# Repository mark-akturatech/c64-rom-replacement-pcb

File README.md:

# Commodore 64 Kernal Replacement Project

## Description

Simple and compact PCB to replace the C64 Kernal (this is how Commodore spell Kernel) ROM with a 27C256 with the original ROM dump and 3 additional alternative ROMs.

## Development

The project is constructed in Kicad. The output files are generated in Gerber format.

## Design

The PCB replaces the Kernal ROM. The PCB plugs in to the Kernal ROM socket. Two switches or a rotary switch may be used to switch between the alternative ROMs.

## EPROM Configuration

The EPROM is segmented as follows:

- 0k-8k Original Kernal ROM (bank 1) Address line 13 LOW; Address line 14 LOW
- 8k-16k Jiffy DOS (bank 2) Address line 13 HIGH; Address line 14 LOW
- 16k-24k Cockroach Turbo ROM [nostalgia reasons] (bank 3) Address line 13 LOW; Address line 14 HIGH
- 24k-32k Dolphin DOS (bank 4) Address line 13 HIGH; Address line 14 HIGH

The ROM configuration I have used is as follows:

- 0k-8k kernal.901227-03
- 8k-16k JiffyDOS_C64
- 16k-24k cockroach_turbo_rom
- 24k-32k dolphin_dos-30

A switch is connected between +5v and address lines 13 adn 14.

## Part List & Build Instructions

2 x 20 contact (only need 12 contact by 20 is more common) Board-to-Board through hole straight pin headers.
For example <https://au.element14.com/amp-te-connectivity/2-826629-0/btb-conn-header-20pos-1row-2-54mm/dp/1580047>
These are soldered to the 2 rows of 12 through-holes on the underside of the board and are used to plug in to the Kernal ROM socket.
Solder these first.

1 x 28 contact DIP 2.5mm x 15.24mm socket. The socket should slightly stand off the board to not interfere with the pin headers.
For example <https://au.element14.com/multicomp/2227mc-28-06-07-f1/socket-ic-dil-0-6-28way/dp/1103852>
This soldered to the topside of the PCB for mounting the 27C256.

1 x 4 position, minimum 2 pole rotary switch or 2 x single throw double miniature toggle switches
For example <https://au.mouser.com/ProductDetail/Alpha-Taiwan/SR2511F-0304-19R0B-E9-N-W-159> OR
<https://au.element14.com/e-switch/100sp1t1b1m1qeh/toggle-switch-spdt-5a-120vac-28vdc/dp/2522278>

1 x 27C256 EPROM (or compatible - eg AT28C256 will also work)
I've used a write once compatible EPROM here.

## Rotary Switch Wiring

If a 4 position rotary switch is used, it is wired as follows:
- Pole A: connected to address line 13
- Pole B: connected to address line 14
- Pins 1, 3, 5 and 6 connected to GND
- Pins 2, 4, 7 and 8 connected to +5V

This should result in the following truth table:
Pos | A13 | A14 | Why
--- | --- | --- | ---
1 | L | L | Pin 1 (Pole A Way 1) Low, Pin 5 (Pole B Way 1) Low
2 | H | L | Pin 2 (Pole A Way 2) High, Pin 6 (Pole B Way 2) Low
3 | L | H | Pin 3 (Pole A Way 3) Low, Pin 7 (Pole B Way 3) High
4 | H | H | Pin 4 (Pole A Way 4) High, Pin 8 (Pole B Way 4) High

## Double Pole Switch Wiring

If using two single throw double pole switches, wire as follows:
- Switch 1: Center pin to address line 13, top pin to GND, bottom pin to +5V.
- Switch 2: Center pin to address line 14, top pin to GND, bottom pin to +5V.

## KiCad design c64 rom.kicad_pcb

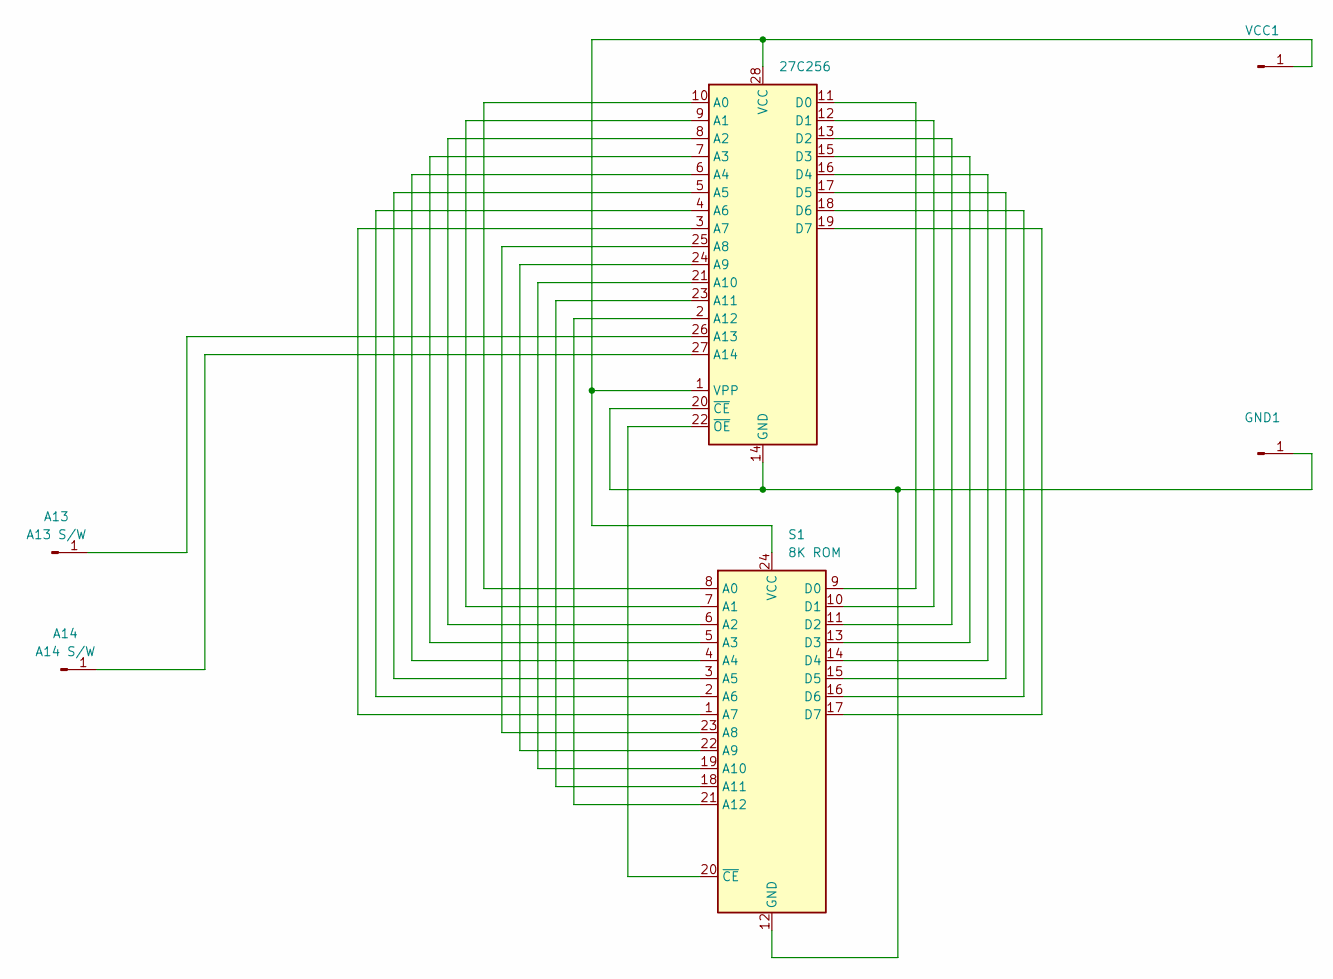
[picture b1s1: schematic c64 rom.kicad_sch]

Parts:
A13: A13 S/W; Pin_D0.7mm_L6.5mm_W1.8mm_FlatFork
A14: A14 S/W; Pin_D0.7mm_L6.5mm_W1.8mm_FlatFork
GND1: GND; Pin_D0.7mm_L6.5mm_W1.8mm_FlatFork
S1: 8K ROM; DIP-24_W15.24mm
U1: 27C256; DIP-28_W15.24mm
VCC1: +5V; Pin_D0.7mm_L6.5mm_W1.8mm_FlatFork

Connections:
unnamed: A13.1, U1.26 (A13)
unnamed: A14.1, U1.27 (A14)
unnamed: GND1.1, S1.12 (GND), U1.14 (GND), U1.20 (~CE)
unnamed: S1.8 (A0), U1.10 (A0)
unnamed: S1.7 (A1), U1.9 (A1)
unnamed: S1.6 (A2), U1.8 (A2)
unnamed: S1.5 (A3), U1.7 (A3)
unnamed: S1.4 (A4), U1.6 (A4)
unnamed: S1.3 (A5), U1.5 (A5)
unnamed: S1.2 (A6), U1.4 (A6)
unnamed: S1.1 (A7), U1.3 (A7)
unnamed: S1.23 (A8), U1.25 (A8)
unnamed: S1.22 (A9), U1.24 (A9)
unnamed: S1.19 (A10), U1.21 (A10)
unnamed: S1.18 (A11), U1.23 (A11)
unnamed: S1.21 (A12), U1.2 (A12)
unnamed: S1.9 (D0), U1.11 (D0)
unnamed: S1.10 (D1), U1.12 (D1)
unnamed: S1.11 (D2), U1.13 (D2)
unnamed: S1.13 (D3), U1.15 (D3)
unnamed: S1.14 (D4), U1.16 (D4)
unnamed: S1.15 (D5), U1.17 (D5)
unnamed: S1.16 (D6), U1.18 (D6)
unnamed: S1.17 (D7), U1.19 (D7)
unnamed: S1.24 (VCC), U1.1 (VPP), U1.28 (VCC), VCC1.1
unnamed: S1.20 (~CE), U1.22 (~OE)

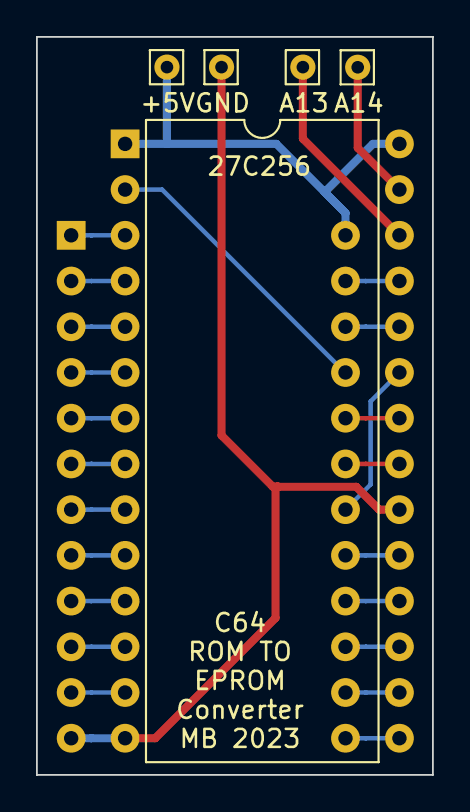
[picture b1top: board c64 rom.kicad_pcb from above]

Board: 2 copper layers, 22.0 x 41.0 mm, 6 parts (0 on the bottom side), 26 nets.

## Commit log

2023-08-02 Main: Fix Incorrect naming of 5V terminal
2023-08-02 Main: added PCB images to readme file
